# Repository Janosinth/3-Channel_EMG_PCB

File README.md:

# 3-Channel_EMG_PCB
A forearm-focused EMG sensor with 3 channels. Useful for identifying finger or general forearm muscle movements.

# Photos 
**3D Render of PCB**

**Fully Populated PCB**

# System Architecture

The design bridges a high-gain, low-noise analog front-end with real-time embedded C++ digital signal processing.

# 1. Analog Front-End (Hardware)
Bio-Amplification: An INA630 instrumentation amplifier interfaces directly with surface electrodes to capture raw muscle action potentials.

Bandpass Filter: Using a TLV9354 operational amplifier, the circuit drives 3 (1 per channel) active bandpass filters with a bandpass of 20 - 500Hz. The bandpass is a combination of a 2nd-order high-pass filter and a first-order low-pass filter. 

Active Precision Rectification: The TLV9354 operational amplifier also drives a full active precision wave rectifier. This mathematically eliminates the forward voltage drop typical of passive Schottky diode envelopes, ensuring extremely weak muscle signals are not lost.

Total System Gain: Fixed hardware gain of ~600x designed to pull isolated bio-signals out of the noise floor before hitting the ADC.

# 2. Digital Signal Processing (Firmware)
Microcontroller: ESP32 operating with a 12-bit ADC configured to ADC_0db (0V - 1.1V range) for maximum microvolt resolution.

Filtering: A real-time C++ Exponential Moving Average (EMA) algorithm processes the raw rectified wave.

Software Scaling: Applies a digital multiplier to map the filtered biological signal to a constrained 0-3.3V logic output for external interfacing or data logging.

# Repository structure
*   `Firmware/` — ESP32 C++ code for digital signal processing. 
    *   `ESP32_Code.ino` — Arduino IDE project folder.
*   `Hardware/` — KiCad 10.0 project files and custom footprints.
    *   `Kicad_Files` — All main KiCad files to open the project.
    *   `EMG2_Stuff.pretty/` — Project-specific dependencies (Custom footprint library (INA630, MAX660, audio jacks).
    *   `Gerbers/` — Prerendered Gerber files from KiCad files ready for use with JLCPCB manufacturing tolerances. 
*   `Simulations/` — Analog circuit verification.
    *   `EMG_Circuit_Simulation.ms14` — Multisim active filter and precision rectifier simulation files.
*   `Video and Image Assets/` — Media and visual documentation.
    *   `KiCad PCB schematic.png` — PCB schematic inside KiCad. 
    *   `Bare PCB.png` — Bare manufactured PCB with no soldered components.
    *   `Full PCB Top Down View.jpg` — Top-down view of fully assembled PCB.
    *   `3D Render.png` — 3D render of the PCB in KiCad.
    *   `Demo Video.gif` — GIF of a portion of the demo video. 

# Setup & Installation
Firmware Deployment:
1. Clone this repository.

2. Open Firmware/ESP32_Code.ino in the Arduino IDE.

3. Select the ESP32 Dev Module board and compile/upload. 

Hardware Viewing:

1. Install KiCad 9.0+.

2. Open the Hardware/EMG2.kicad_pro file using KiCad, ensuring that the EMG2_Stuff.pretty EMG2.kicad_pro file is under the Hardware file directory. 

Note: Ensure the Libraries/EMG2_Stuff.pretty footprint directory is properly linked in your KiCad Footprint Library configuration to prevent "missing footprint" errors when viewing the PCB layout.

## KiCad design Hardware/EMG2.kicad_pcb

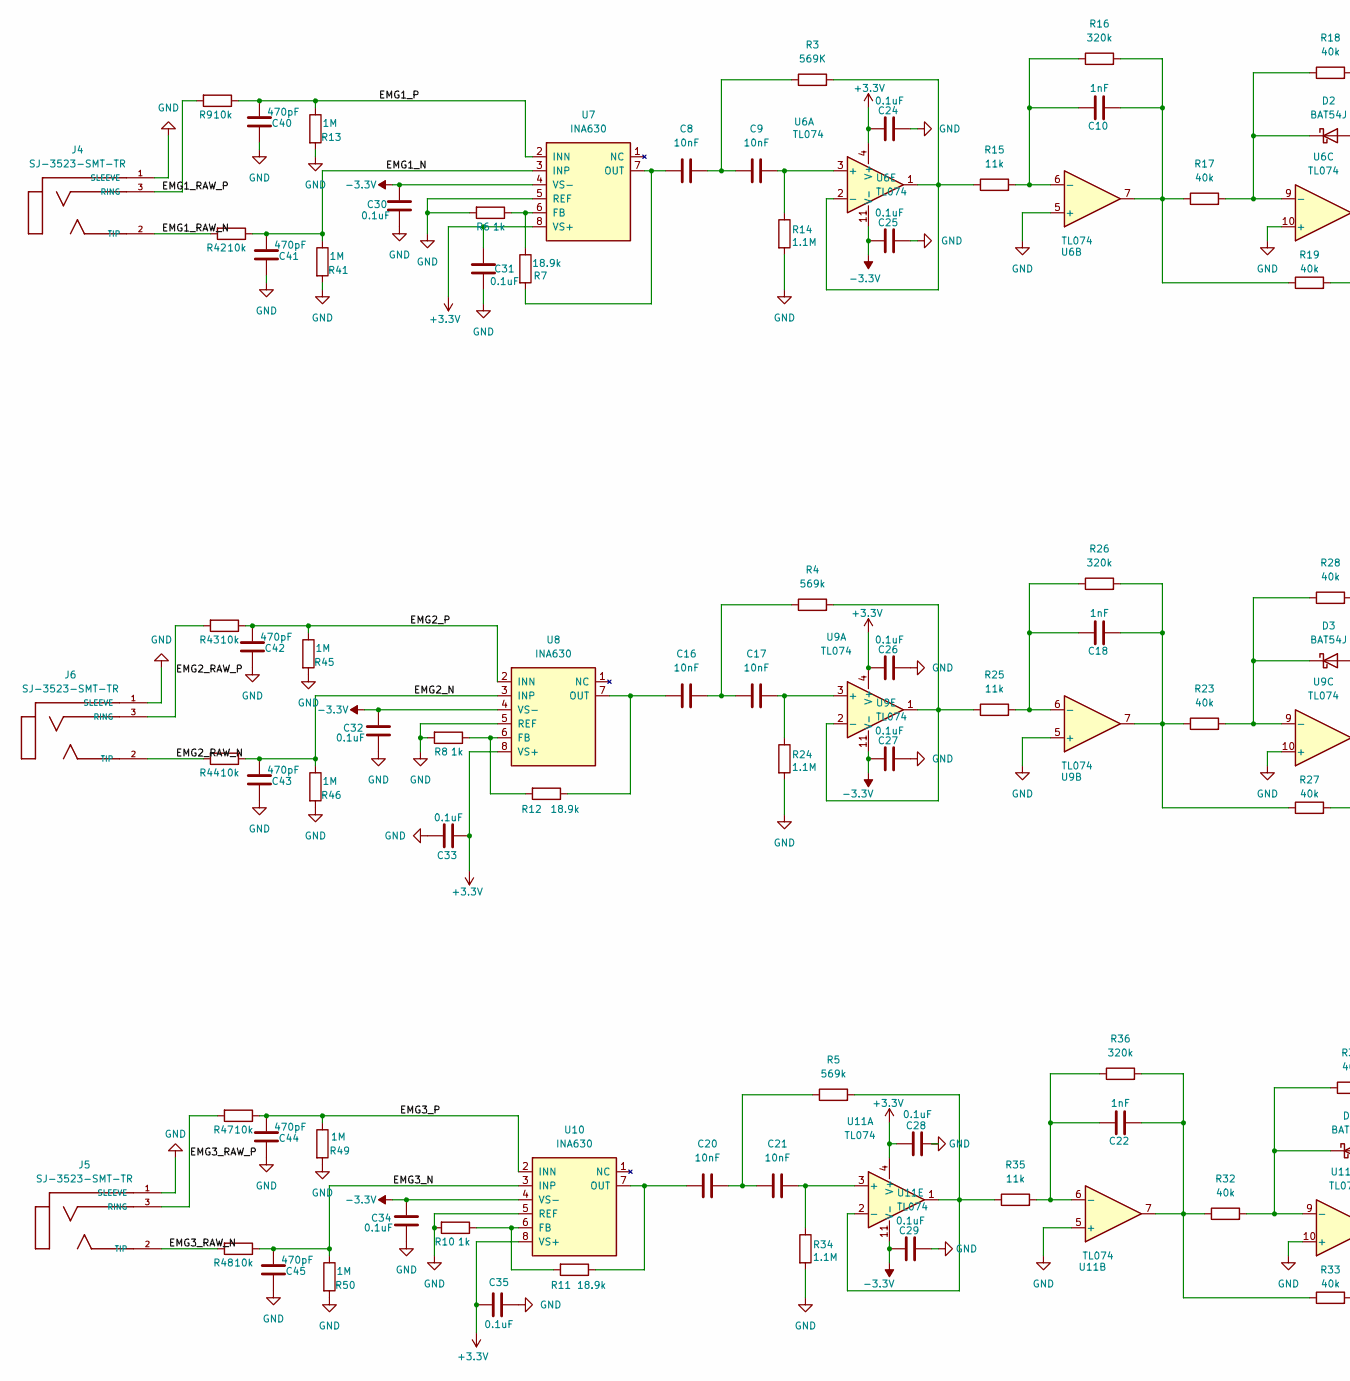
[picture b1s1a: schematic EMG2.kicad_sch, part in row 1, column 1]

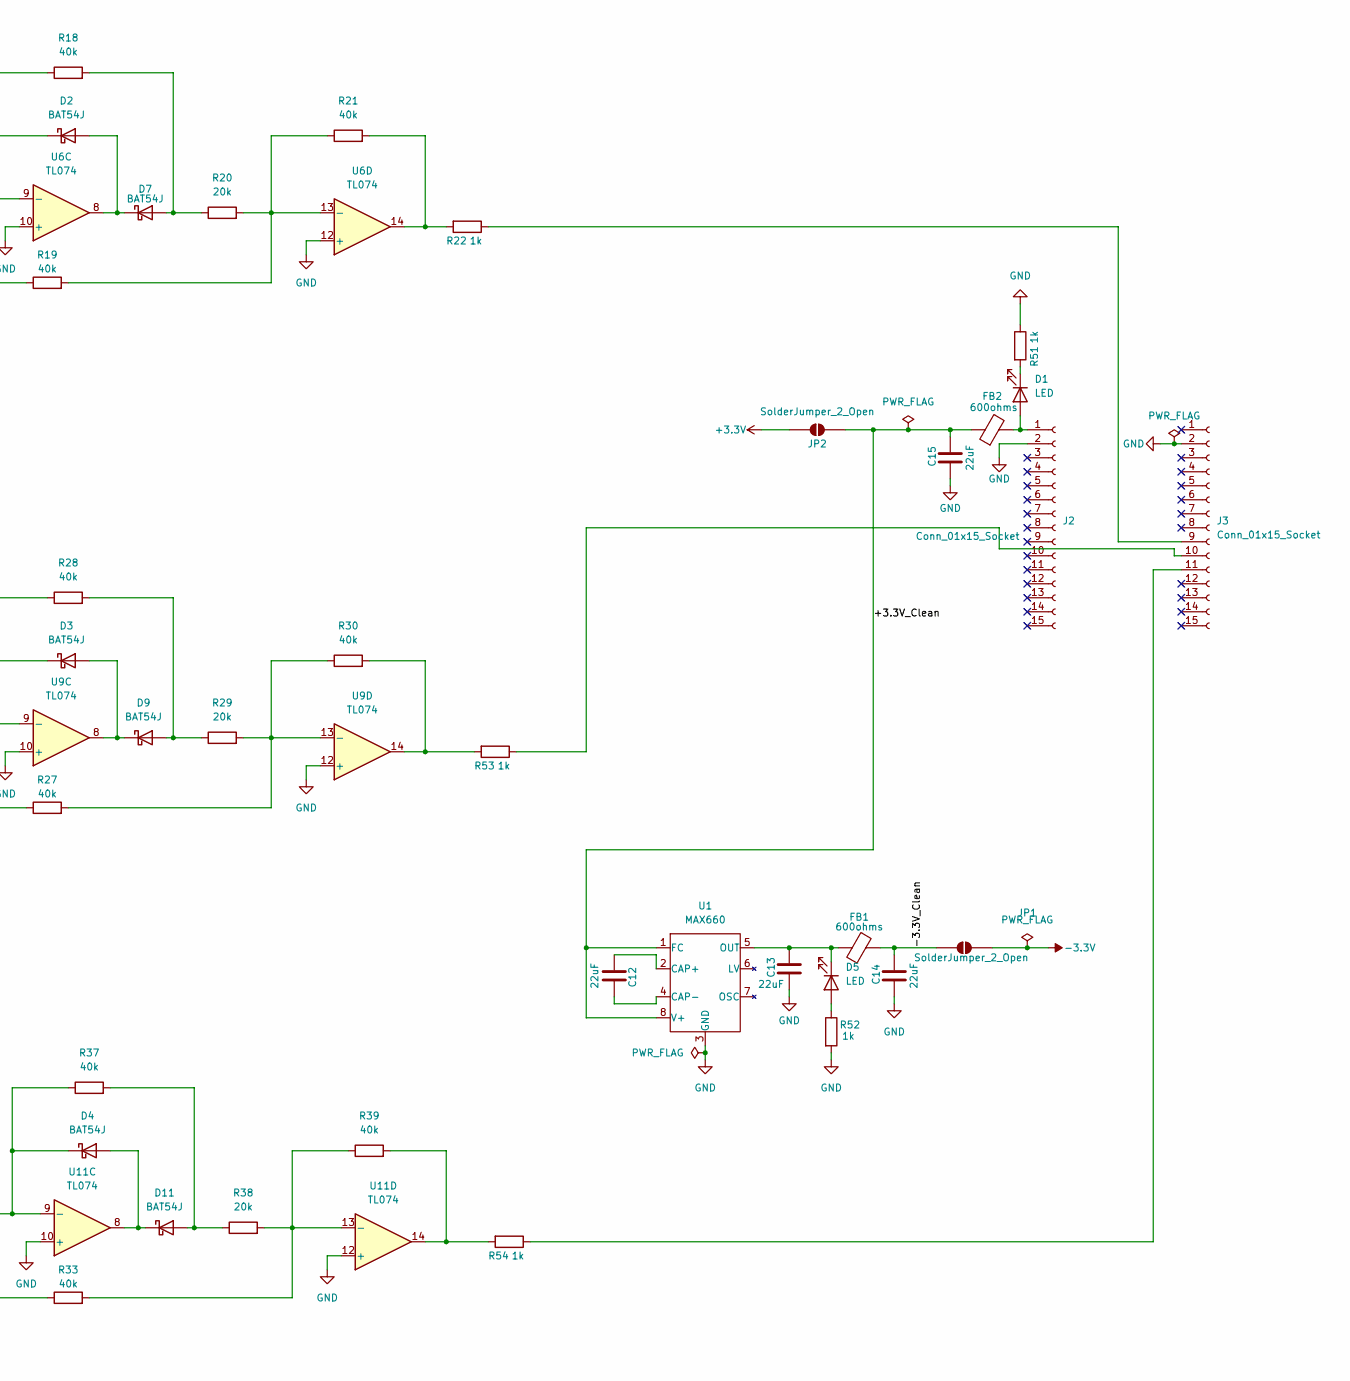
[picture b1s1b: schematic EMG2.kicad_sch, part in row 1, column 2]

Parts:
C8, C9, C16, C17, C20, C21: 10nF; C_0805_2012Metric
C10, C18, C22: 1nF; C_0805_2012Metric
C12, C13, C14, C15: 22uF; C_0805_2012Metric
C24, C25, C26, C27, C28, C29, C30, C31, C32, C33, C34, C35: 0.1uF; C_0805_2012Metric
C40, C41, C42, C43, C44, C45: 470pF; C_0805_2012Metric
D1, D5: LED; LED_0805_2012Metric
D2, D3, D4, D7, D9, D11: BAT54J; D_SOD-323
FB1, FB2: 600ohms; L_0805_2012Metric
J2, J3: Conn_01x15_Socket; PinSocket_1x15_P2.54mm_Vertical
J4, J5, J6: SJ-3523-SMT-TR; CUI_SJ-3523-SMT-TR
JP1, JP2: SolderJumper_2_Open; SolderJumper-2_P1.3mm_Open_RoundedPad1.0x1.5mm
R3: 569K; R_0603_1608Metric
R4, R5: 569k; R_0603_1608Metric
R6, R8, R10, R22, R51, R52, R53, R54: 1k; R_0805_2012Metric
R7, R11, R12: 18.9k; R_0603_1608Metric
R9, R42, R43, R44, R47, R48: 10k; R_0805_2012Metric
R13, R41, R45, R46, R49, R50: 1M; R_0805_2012Metric
R14, R24, R34: 1.1M; R_0805_2012Metric
R15, R25, R35: 11k; R_0603_1608Metric
R16, R26, R36: 320k; R_0603_1608Metric
R17, R18, R19, R21, R23, R27, R28, R30, R32, R33, R37, R39: 40k; R_0805_2012Metric
R20, R29, R38: 20k; R_0805_2012Metric
U1: MAX660; SOIC-8_3.9x4.9mm_P1.27mm
U6, U9, U11: TL074; SOIC-14_3.9x8.7mm_P1.27mm
U7, U8, U10: INA630; TSOT-23-8

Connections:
+3.3V: C24.1, C26.1, C28.1, C31.1, C33.1, C35.1, JP2.2 (B), U6.4 (V+), U7.8 (VS+), U8.8 (VS+), U9.4 (V+), U10.8 (VS+), U11.4 (V+)
-3.3V: C25.1, C27.1, C29.1, C30.1, C32.1, C34.1, JP1.2 (B), U6.11 (V-), U7.4 (VS-), U8.4 (VS-), U9.11 (V-), U10.4 (VS-), U11.11 (V-)
/+3.3V_Clean: C15.1, FB2.1, JP2.1 (A), U1.1 (FC), U1.8 (V+)
/-3.3V_Clean: C14.1, FB1.2, JP1.1 (A)
/EMG1_N: C41.2, R41.1, R42.1, U7.3 (INP)
/EMG1_P: C40.2, R9.1, R13.1, U7.2 (INN)
/EMG1_RAW_N: J4.2 (TIP), R42.2
/EMG1_RAW_P: J4.3 (RING), R9.2
/EMG2_N: C43.2, R44.1, R46.1, U8.3 (INP)
/EMG2_P: C42.2, R43.1, R45.1, U8.2 (INN)
/EMG2_RAW_N: J6.2 (TIP), R44.2
/EMG2_RAW_P: J6.3 (RING), R43.2
/EMG3_N: C45.2, R48.1, R50.1, U10.3 (INP)
/EMG3_P: C44.2, R47.1, R49.1, U10.2 (INN)
/EMG3_RAW_N: J5.2 (TIP), R48.2
/EMG3_RAW_P: J5.3 (RING), R47.2
GND: C13.2, C14.2, C15.2, C24.2, C25.2, C26.2, C27.2, C28.2, C29.2, C30.2, C31.2, C32.2, C33.2, C34.2, C35.2, C40.1, C41.1, C42.1, C43.1, C44.1, C45.1, J2.2, J3.2, J4.1 (SLEEVE), J5.1 (SLEEVE), J6.1 (SLEEVE), R6.2, R8.2, R10.2, R13.2, R14.2, R24.2, R34.2, R41.2, R45.2, R46.2, R49.2, R50.2, R51.1, R52.2, U1.3 (GND), U6.5 (+), U6.10 (+), U6.12 (+), U7.5 (REF), U8.5 (REF), U9.5 (+), U9.10 (+), U9.12 (+), U10.5 (REF), U11.5 (+), U11.10 (+), U11.12 (+)
unnamed: C8.2, C9.1, R3.1
unnamed: C10.2, R16.2, R17.1, R19.1, U6.7
unnamed: C16.2, C17.1, R4.1
unnamed: C18.2, R23.1, R26.2, R27.1, U9.7
unnamed: C20.2, C21.1, R5.1
unnamed: C22.2, R32.1, R33.1, R36.2, U11.7
unnamed: D1.2 (A), FB2.2, J2.1
unnamed: D1.1 (K), R51.2
unnamed: D2.2 (A), D7.1 (K), U6.8
unnamed: D2.1 (K), R17.2, R18.1, U6.9 (-)
unnamed: D3.2 (A), D9.1 (K), U9.8
unnamed: D3.1 (K), R23.2, R28.1, U9.9 (-)
unnamed: D4.1 (K), R32.2, R37.1, U11.9 (-)
unnamed: D5.2 (A), R52.1
unnamed: C13.1, D5.1 (K), FB1.1, U1.5 (OUT)
unnamed: D7.2 (A), R18.2, R20.1
unnamed: D9.2 (A), R28.2, R29.1
unnamed: D11.2 (A), R37.2, R38.1
unnamed: D4.2 (A), D11.1 (K), U11.8
unnamed: J3.9, R22.1
unnamed: J3.10, R53.1
unnamed: J3.11, R54.1
unnamed: R21.2, R22.2, U6.14
unnamed: R30.2, R53.2, U9.14
unnamed: R39.2, R54.2, U11.14
unnamed: C12.2, U1.2 (CAP+)
unnamed: C12.1, U1.4 (CAP-)
unnamed: C9.2, R14.1, U6.3 (+)
unnamed: R3.2, R15.1, U6.1, U6.2 (-)
unnamed: C10.1, R15.2, R16.1, U6.6 (-)
unnamed: R19.2, R20.2, R21.1, U6.13 (-)
unnamed: R6.1, R7.1, U7.6 (FB)
unnamed: C8.1, R7.2, U7.7 (OUT)
unnamed: R8.1, R12.2, U8.6 (FB)
unnamed: C16.1, R12.1, U8.7 (OUT)
unnamed: C17.2, R24.1, U9.3 (+)
unnamed: R4.2, R25.1, U9.1, U9.2 (-)
unnamed: C18.1, R25.2, R26.1, U9.6 (-)
unnamed: R27.2, R29.2, R30.1, U9.13 (-)
unnamed: R10.1, R11.2, U10.6 (FB)
unnamed: C20.1, R11.1, U10.7 (OUT)
unnamed: C21.2, R34.1, U11.3 (+)
unnamed: R5.2, R35.1, U11.1, U11.2 (-)
unnamed: C22.1, R35.2, R36.1, U11.6 (-)
unnamed: R33.2, R38.2, R39.1, U11.13 (-)

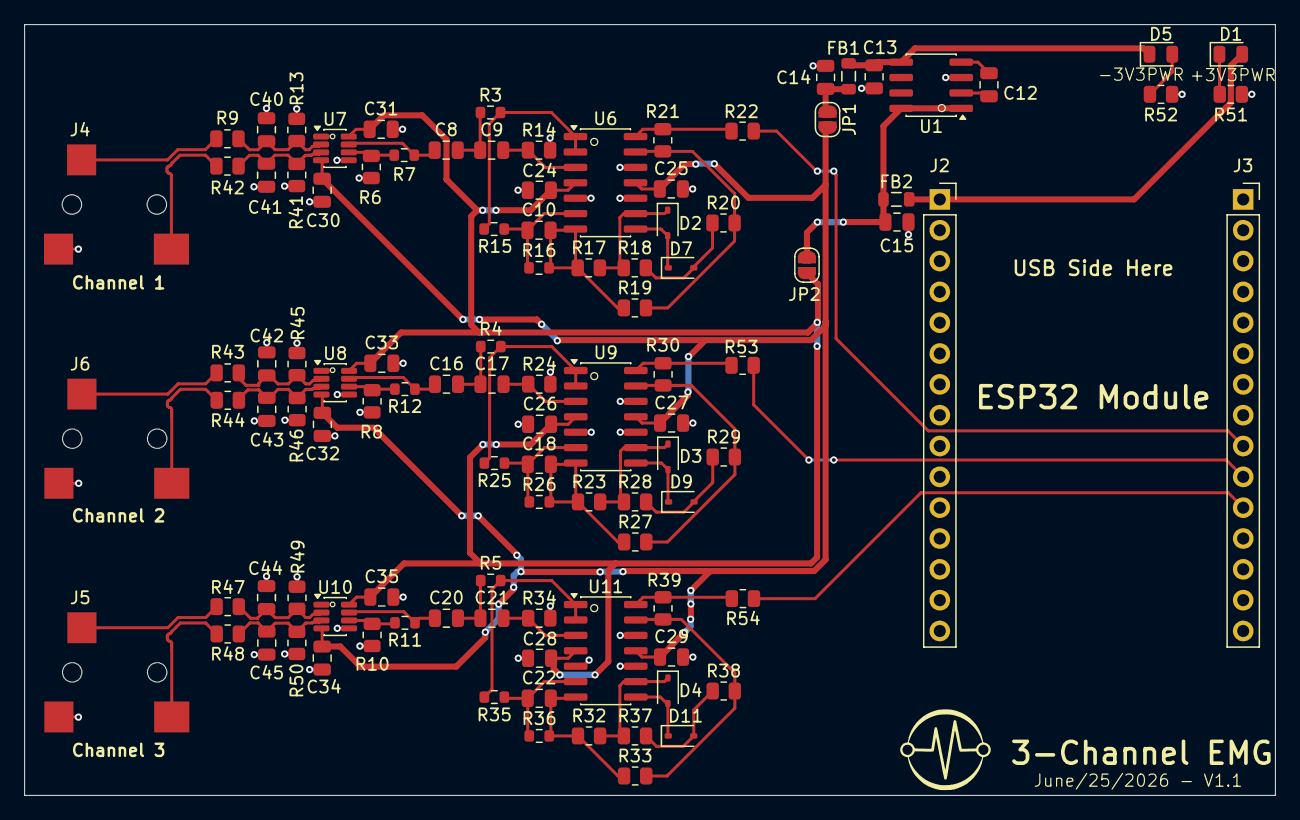
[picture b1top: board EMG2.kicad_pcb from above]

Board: 4 copper layers, 103.1 x 63.5 mm, 105 parts (0 on the bottom side), 62 nets.
